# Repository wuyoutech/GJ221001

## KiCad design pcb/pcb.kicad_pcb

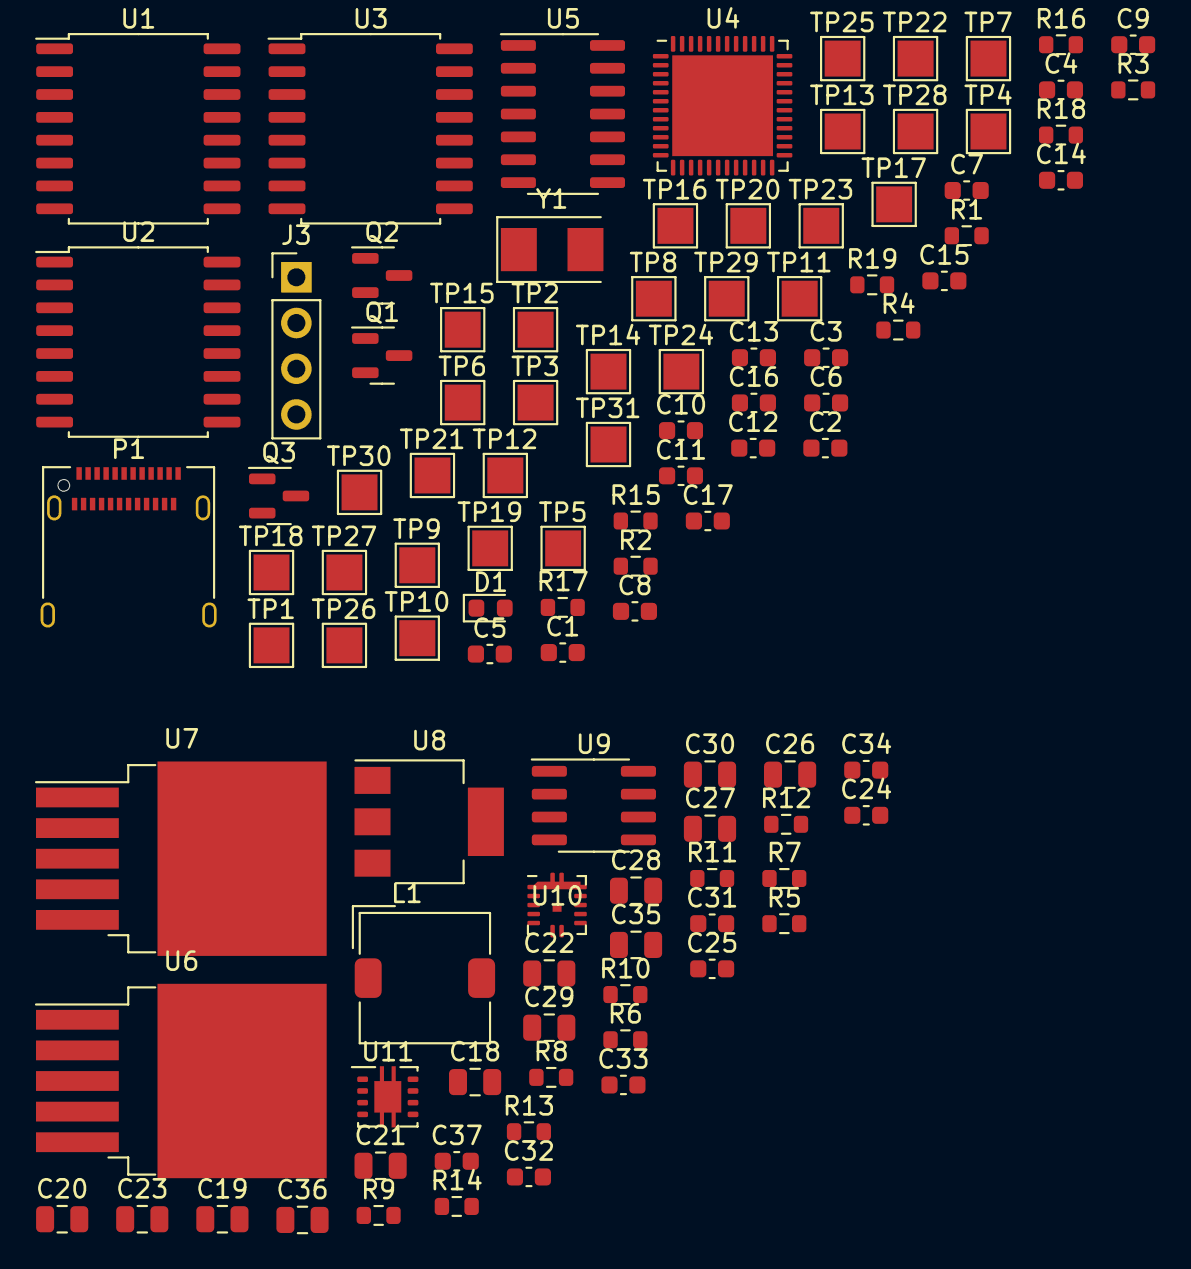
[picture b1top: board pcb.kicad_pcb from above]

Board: 2 copper layers, 106 parts (0 on the bottom side), 73 nets, no tracks yet.

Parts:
C1, C2, C3, C4, C5, C6, C7, C11, C12, C13, C14, C15, C16, C17, C24, C31: 100nF; C_0603_1608Metric
C8: 2.2uF; C_0603_1608Metric
C9, C10: 8pF; C_0603_1608Metric
C18, C29, C35, C36: 22uF; C_0805_2012Metric
C19: 10uF 50V; C_0805_2012Metric
C20, C21, C22: 10uF 25V; C_0805_2012Metric
C23: 10uF; C_0805_2012Metric
C25, C33, C37: 1uF; C_0603_1608Metric
C26, C30: 100uF 25V; C_0805_2012Metric
C27: 22uF 50V; C_0805_2012Metric
C28: 22uF 15V; C_0805_2012Metric
C32: 22nF; C_0603_1608Metric
C34: 10nF; C_0603_1608Metric
D1: LED; D_0603_1608Metric
J3: debug; PinHeader_1x04_P2.54mm_Vertical
L1: 2uH; L_TDK_SLF7055
P1: USB_C_Plug_USB2.0; USB_C_Receptacle_Amphenol_12401610E4-2A
Q1, Q2, Q3: FH3415S; SOT-23
R1, R10: 0R; R_0603_1608Metric
R2, R15, R16, R17: 10K; R_0603_1608Metric
R3: 1.5K; R_0603_1608Metric
R4: 120R; R_0603_1608Metric
R5: 8K; R_0603_1608Metric
R6: 910; R_0603_1608Metric
R7: 82; R_0603_1608Metric
R8: 300; R_0603_1608Metric
R9: 180; R_0603_1608Metric
R11: 180K; R_0603_1608Metric
R12: 20K; R_0603_1608Metric
R13: 390K; R_0603_1608Metric
R14: 120K; R_0603_1608Metric
R18, R19: 22R; R_0603_1608Metric
TP1: +16V; TestPoint_Pad_2.0x2.0mm
TP2, TP23, TP29, TP31: GND; TestPoint_Pad_2.0x2.0mm
TP3: A; TestPoint_Pad_2.0x2.0mm
TP4: B; TestPoint_Pad_2.0x2.0mm
TP5: Z; TestPoint_Pad_2.0x2.0mm
TP6: Y; TestPoint_Pad_2.0x2.0mm
TP7: 1; TestPoint_Pad_2.0x2.0mm
TP8: 2; TestPoint_Pad_2.0x2.0mm
TP9: 3; TestPoint_Pad_2.0x2.0mm
TP10: 4; TestPoint_Pad_2.0x2.0mm
TP11: 5; TestPoint_Pad_2.0x2.0mm
TP12: 6; TestPoint_Pad_2.0x2.0mm
TP13: 7; TestPoint_Pad_2.0x2.0mm
TP14: 8; TestPoint_Pad_2.0x2.0mm
TP15: 9; TestPoint_Pad_2.0x2.0mm
TP16: 10; TestPoint_Pad_2.0x2.0mm
TP17, TP18, TP19, TP20, TP21: 6V; TestPoint_Pad_2.0x2.0mm
TP22: 3.3V; TestPoint_Pad_2.0x2.0mm
TP24: +15V; TestPoint_Pad_2.0x2.0mm
TP25: SW; TestPoint_Pad_2.0x2.0mm
TP26: ATT1; TestPoint_Pad_2.0x2.0mm
TP27: ATT2; TestPoint_Pad_2.0x2.0mm
TP28: PA_SW; TestPoint_Pad_2.0x2.0mm
TP30: dc_6v; TestPoint_Pad_2.0x2.0mm
U1, U2, U3: SSP5840ED; SOIC-16W_7.5x10.3mm_P1.27mm
U4: STM32F411CEUx; QFN-48-1EP_7x7mm_P0.5mm_EP5.6x5.6mm
U5: MAX3491; SOIC-14_3.9x8.7mm_P1.27mm
U6, U7: MIC29302WU; TO-263-5_TabPin3
U8: AMS1117-3.3; SOT-223-3_TabPin2
U9: LT1054L; SOIC-8_3.9x4.9mm_P1.27mm
U10: MP2229; MPS_QFN-14
U11: TPS7A3001DRBx; Texas_S-PVSON-N8_1
Y1: 25MHz; Crystal_SMD_5032-2Pin_5.0x3.2mm

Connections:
+3.3V: C1.1, C2.1, C3.1, C11.1, C12.1, C13.1, C14.1, C15.1, C16.1, C17.1, C25.1, C29.1, J3.1, R2.1, R3.1, U1.1 (VCC1), U2.1 (VCC1), U3.1 (VCC1), U4.1 (VBAT), U4.9 (VDDA), U4.24 (VDD), U4.36 (VDD), U4.48 (VDD), U5.13 (VCC), U5.14 (VCC), U8.2 (VO)
+3.3VA: C28.1, Q2.3 (S), R8.1, R16.1, U7.4 (VOUT)
+6V: C20.1, C21.1, C22.1, C35.1, C36.1, L1.2, Q1.3 (S), Q3.3 (S), R11.2, R15.1, R17.1, U7.1 (EN), U7.2 (VIN), U8.3 (VI), U9.8 (V+)
+15V: C27.1, R6.1, TP24.1, U6.4 (VOUT)
-5V: C5.2, C6.2, C7.2, C37.1, R13.1, U1.9 (GND2), U1.15 (GND2), U2.9 (GND2), U2.15 (GND2), U3.9 (GND2), U3.15 (GND2), U11.1 (OUT)
/DIO1: U1.3 (INA), U4.18 (PB0)
/DIO2: U1.4 (INB), U4.19 (PB1)
/DIO3: U1.5 (INC), U4.20 (PB2)
/DIO4: U1.6 (IND), U4.39 (PB3)
/DIO5: U2.3 (INA), U4.40 (PB4)
/DIO6: U2.4 (INB), U4.41 (PB5)
/DIO7: U2.5 (INC), U4.42 (PB6)
/DIO8: U2.6 (IND), U4.43 (PB7)
/DIO9: U3.3 (INA), U4.45 (PB8)
/DIO10: U3.4 (INB), U4.46 (PB9)
/DIO11: U3.5 (INC), U4.21 (PB10)
/DIO12: U3.6 (IND), U4.25 (PB12)
GND: C1.2, C2.2, C3.2, C4.2, C5.1, C6.1, C7.1, C8.2, C9.2, C10.2, C11.2, C12.2, C13.2, C14.2, C15.2, C16.2, C17.2, C18.2, C19.2, C20.2, C21.2, C22.2, C23.2, C24.2, C25.2, C27.2, C28.2, C29.2, C30.2, C32.2, C33.2, C34.2, C35.2, C36.2, C37.2, J3.4, P1.A1 (GND), P1.A12 (GND), P1.B1 (GND), P1.B12 (GND), P1.S1 (SHIELD), R1.2, R5.2, R7.2, R9.2, R12.1, R14.2, TP2.1, TP23.1, TP29.1, TP31.1, U1.2 (GND1), U1.8 (GND1), U1.10 (EN), U1.16 (VCC2), U2.2 (GND1), U2.8 (GND1), U2.10 (EN), U2.16 (VCC2), U3.2 (GND1), U3.8 (GND1), U3.10 (EN), U3.16 (VCC2), U4.8 (VSSA), U4.23 (VSS), U4.35 (VSS), U4.47 (VSS), U4.49 (VSS), U5.6 (GND), U5.7 (GND), U6.3 (GND), U7.3 (GND), U8.1 (GND), U9.3 (GND), U10.1 (GND), U10.5 (LPM), U10.12 (GND), U10.13 (GND), U10.14 (GND), U11.4 (GND), U11.9 (Pad)
IN: C18.1, C19.1, C23.1, TP1.1, U6.1 (EN), U6.2 (VIN), U10.3 (IN), U10.15 (IN)
unnamed: C4.1, R2.2, U4.7 (NRST)
unnamed: C8.1, U4.22 (VCAP1)
unnamed: C9.1, U4.5 (PH0), Y1.2
unnamed: C10.1, U4.6 (PH1), Y1.1
unnamed: C24.1, U10.9 (VCC)
unnamed: C26.1, U9.2 (CAP+)
unnamed: C26.2, U9.4 (CAP-)
unnamed: C30.1, C33.1, U9.5 (-VOUT), U11.5 (EN), U11.8 (IN)
unnamed: C31.1, U10.10 (BST)
unnamed: C31.2, L1.1, U10.2 (SW), U10.11 (SW)
unnamed: C32.1, U10.7 (SS)
unnamed: C34.1, U11.6 (NR/SS)
unnamed: D1.1 (K), U4.2 (PC13)
unnamed: D1.2 (A), R3.2
unnamed: J3.2, U4.34 (PA13)
unnamed: J3.3, U4.37 (PA14)
unnamed: P1.A6 (D+), R19.2
unnamed: P1.A7 (D-), R18.2
unnamed: Q1.1 (D), TP17.1, TP18.1, TP19.1, TP20.1, TP21.1
unnamed: Q1.2 (G), R15.2, U4.10 (PA0)
unnamed: Q2.1 (D), TP22.1
unnamed: Q2.2 (G), R16.2, U4.11 (PA1)
unnamed: Q3.1 (D), TP30.1
unnamed: Q3.2 (G), R17.2, U4.12 (PA2)
unnamed: R1.1, U4.44 (BOOT0)
unnamed: R4.1, TP3.1, U5.12 (A)
unnamed: R4.2, TP4.1, U5.11 (B)
unnamed: R5.1, U10.8 (FREQ/SYNC)
unnamed: R6.2, R7.1, U6.5 (ADJ)
unnamed: R8.2, R9.1, U7.5 (ADJ)
unnamed: R10.1, U10.6 (FB)
unnamed: R10.2, R11.1, R12.2
unnamed: R13.2, R14.1, U11.2 (FB)
unnamed: R18.1, U4.32 (PA11)
unnamed: R19.1, U4.33 (PA12)
unnamed: TP5.1, U5.10 (Z)
unnamed: TP6.1, U5.9 (Y)
unnamed: TP7.1, U1.14 (OUTA)
unnamed: TP8.1, U1.13 (OUTB)
unnamed: TP9.1, U1.12 (OUTC)
unnamed: TP10.1, U1.11 (OUTD)
unnamed: TP11.1, U2.14 (OUTA)
unnamed: TP12.1, U2.13 (OUTB)
unnamed: TP13.1, U2.12 (OUTC)
unnamed: TP14.1, U2.11 (OUTD)
unnamed: TP15.1, U3.14 (OUTA)
unnamed: TP16.1, U3.13 (OUTB)
unnamed: TP25.1, U4.13 (PA3)
unnamed: TP26.1, U4.14 (PA4)
unnamed: TP27.1, U4.15 (PA5)
unnamed: TP28.1, U4.16 (PA6)
unnamed: U4.29 (PA8), U5.3 (~RE), U5.4 (DE)
unnamed: U4.30 (PA9), U5.5 (DI)
unnamed: U4.31 (PA10), U5.2 (RO)

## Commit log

2022-10-19 add hardware designs
2022-10-25 add power tree
2022-10-27 [temp]
2022-10-28 [feature] sch finish
2022-10-28 [bugfix] fix debug interface and usb
2022-10-29 [sch] finish footprint assignment
2022-10-29 [pcb] import pcb from sch
2022-10-29 add test
